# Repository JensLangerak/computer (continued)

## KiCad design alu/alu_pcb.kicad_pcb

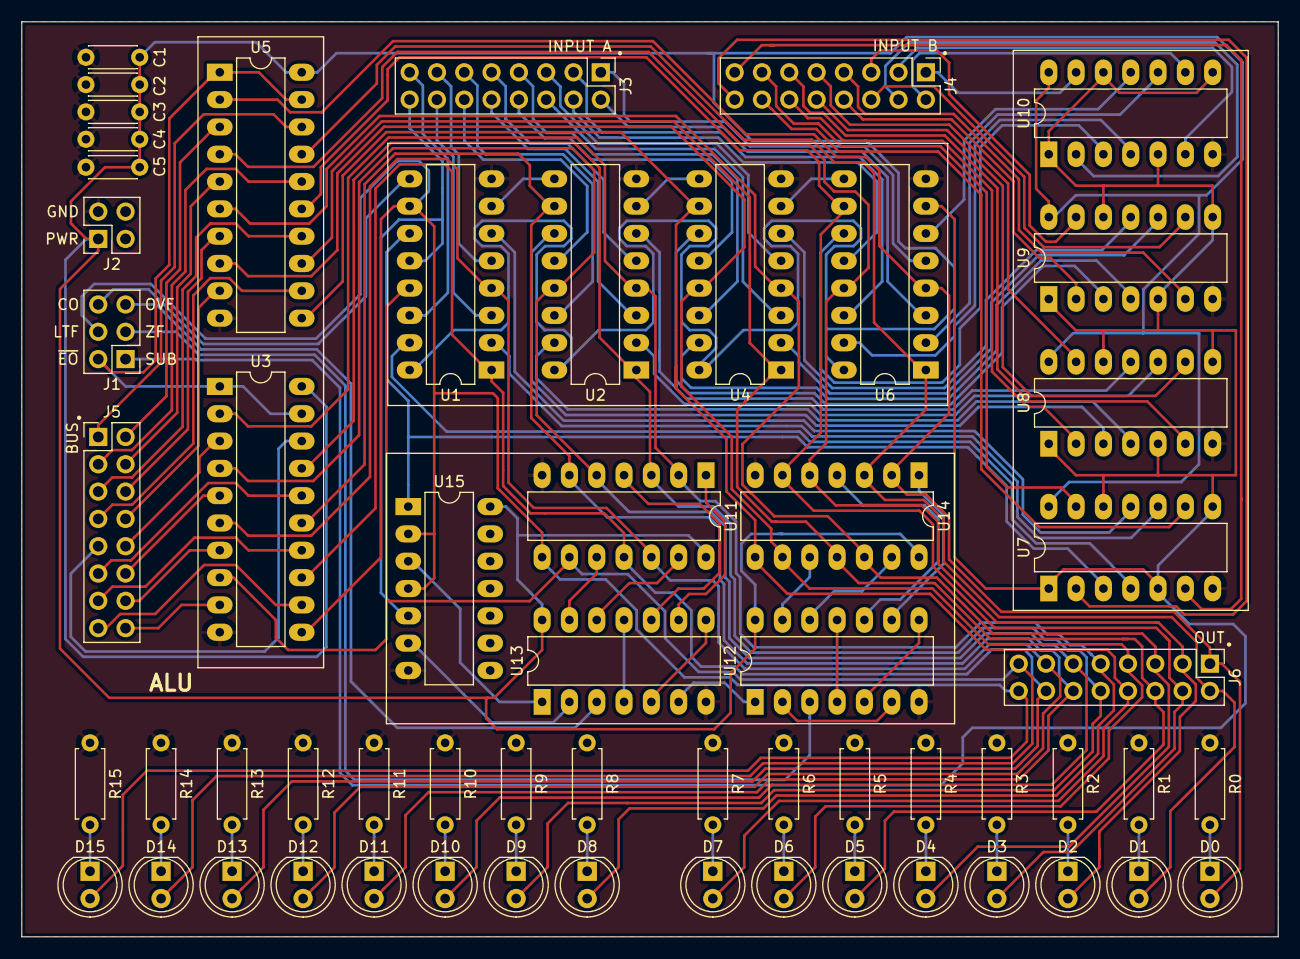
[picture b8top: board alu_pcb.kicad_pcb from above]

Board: 2 copper layers, 116.8 x 85.1 mm, 58 parts (0 on the bottom side), 122 nets.

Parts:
C1, C2, C3, C4, C5: 0.1µF; C_Disc_D4.3mm_W1.9mm_P5.00mm
D0, D1, D2, D3, D4, D5, D6, D7, D8, D9, D10, D11, D12, D13, D14, D15: LED_ALT; LED_D5.0mm
J1: Conn_02x03_Odd_Even; PinHeader_2x03_P2.54mm_Vertical
J2: Conn_02x02_Odd_Even; PinHeader_2x02_P2.54mm_Vertical
J3, J4, J5, J6: Conn_02x08_Odd_Even; PinHeader_2x08_P2.54mm_Vertical
R0, R1, R2, R3, R4, R5, R6, R7, R8, R9, R10, R11, R12, R13, R14, R15: 5k; R_Axial_DIN0207_L6.3mm_D2.5mm_P7.62mm_Horizontal
U1, U2, U4, U6: 74LS283; DIP-16_W7.62mm_LongPads
U3, U5: 74LS244; DIP-20_W7.62mm_LongPads
U7, U8, U9, U10: 74LS386; DIP-14_W7.62mm_LongPads
U11, U14: 74LS02; DIP-14_W7.62mm_LongPads
U12, U13: 74LS08; DIP-14_W7.62mm_LongPads
U15: 74LS00; DIP-14_W7.62mm_LongPads

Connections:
/ALU/CARRY_OUT: J1.6, U1.9
/ALU/D_BI0: U6.6, U10.11
/ALU/D_BI1: U6.2, U10.10
/ALU/D_BI2: U6.15, U10.4
/ALU/D_BI3: U6.11, U10.3
/ALU/D_BI4: U4.6, U9.11
/ALU/D_BI5: U4.2, U9.10
/ALU/D_BI6: U4.15, U9.4
/ALU/D_BI7: U4.11, U9.3
/ALU/D_BI8: U2.6, U8.11
/ALU/D_BI9: U2.2, U8.10
/ALU/D_BI10: U2.15, U8.4
/ALU/D_BI11: U2.11, U8.3
/ALU/D_BI12: U1.6, U7.11
/ALU/D_BI13: U1.2, U7.10
/ALU/D_BI14: U1.15, U7.4
/ALU/D_BI15: U1.11, U7.3, U15.1
/ALU/LTF: D15.2, J1.4, J6.16, U1.10, U3.11, U11.8, U15.2, U15.4
/ALU/OVF: J1.5, U13.3
/ALU/SUBTRACT: J1.1, U6.7, U7.1, U7.5, U7.8, U7.12, U8.1, U8.5, U8.8, U8.12, U9.1, U9.5, U9.8, U9.12, U10.1, U10.5, U10.8, U10.12
/ALU/ZF: J1.3, U12.3
/ALU/~ENALBE_OUTPUT~: J1.2, U3.1, U3.19, U5.1, U5.19
/CONN BUS A/D0: J3.1, U6.5
/CONN BUS A/D1: J3.2, U6.3
/CONN BUS A/D2: J3.3, U6.14
/CONN BUS A/D3: J3.4, U6.12
/CONN BUS A/D4: J3.5, U4.5
/CONN BUS A/D5: J3.6, U4.3
/CONN BUS A/D6: J3.7, U4.14
/CONN BUS A/D7: J3.8, U4.12
/CONN BUS A/D8: J3.9, U2.5
/CONN BUS A/D9: J3.10, U2.3
/CONN BUS A/D10: J3.11, U2.14
/CONN BUS A/D11: J3.12, U2.12
/CONN BUS A/D12: J3.13, U1.5
/CONN BUS A/D13: J3.14, U1.3
/CONN BUS A/D14: J3.15, U1.14
/CONN BUS A/D15: J3.16, U1.12, U15.5
/CONN BUS B/D0: J4.1, U10.13
/CONN BUS B/D1: J4.2, U10.9
/CONN BUS B/D2: J4.3, U10.6
/CONN BUS B/D3: J4.4, U10.2
/CONN BUS B/D4: J4.5, U9.13
/CONN BUS B/D5: J4.6, U9.9
/CONN BUS B/D6: J4.7, U9.6
/CONN BUS B/D7: J4.8, U9.2
/CONN BUS B/D8: J4.9, U8.13
/CONN BUS B/D9: J4.10, U8.9
/CONN BUS B/D10: J4.11, U8.6
/CONN BUS B/D11: J4.12, U8.2
/CONN BUS B/D12: J4.13, U7.13
/CONN BUS B/D13: J4.14, U7.9
/CONN BUS B/D14: J4.15, U7.6
/CONN BUS B/D15: J4.16, U7.2
/CONN BUS DATA/D0: J5.1, U5.18
/CONN BUS DATA/D1: J5.2, U5.3
/CONN BUS DATA/D2: J5.3, U5.16
/CONN BUS DATA/D3: J5.4, U5.5
/CONN BUS DATA/D4: J5.5, U5.14
/CONN BUS DATA/D5: J5.6, U5.7
/CONN BUS DATA/D6: J5.7, U5.12
/CONN BUS DATA/D7: J5.8, U5.9
/CONN BUS DATA/D8: J5.9, U3.18
/CONN BUS DATA/D9: J5.10, U3.3
/CONN BUS DATA/D10: J5.11, U3.16
/CONN BUS DATA/D11: J5.12, U3.5
/CONN BUS DATA/D12: J5.13, U3.14
/CONN BUS DATA/D13: J5.14, U3.7
/CONN BUS DATA/D14: J5.15, U3.12
/CONN BUS DATA/D15: J5.16, U3.9
/CONN BUS SUM/D0: D0.2, J6.1, U5.2, U6.4, U14.2
/CONN BUS SUM/D1: D1.2, J6.2, U5.17, U6.1, U14.3
/CONN BUS SUM/D2: D2.2, J6.3, U5.4, U6.13, U14.5
/CONN BUS SUM/D3: D3.2, J6.4, U5.15, U6.10, U14.6
/CONN BUS SUM/D4: D4.2, J6.5, U4.4, U5.6, U14.12
/CONN BUS SUM/D5: D5.2, J6.6, U4.1, U5.13, U14.11
/CONN BUS SUM/D6: D6.2, J6.7, U4.13, U5.8, U14.9
/CONN BUS SUM/D7: D7.2, J6.8, U4.10, U5.11, U14.8
/CONN BUS SUM/D8: D8.2, J6.9, U2.4, U3.2, U11.2
/CONN BUS SUM/D9: D9.2, J6.10, U2.1, U3.17, U11.3
/CONN BUS SUM/D10: D10.2, J6.11, U2.13, U3.4, U11.5
/CONN BUS SUM/D11: D11.2, J6.12, U2.10, U3.15, U11.6
/CONN BUS SUM/D12: D12.2, J6.13, U1.4, U3.6, U11.12
/CONN BUS SUM/D13: D13.2, J6.14, U1.1, U3.13, U11.11
/CONN BUS SUM/D14: D14.2, J6.15, U1.13, U3.8, U11.9
GND: C1.1, C2.1, C3.1, C4.1, C5.1, J2.2, R0.1, R1.1, R2.1, R3.1, R4.1, R5.1, R6.1, R7.1, R8.1, R9.1, R10.1, R11.1, R12.1, R13.1, R14.1, R15.1, U1.8, U2.8, U3.10, U4.8, U5.10, U6.8, U7.7, U8.7, U9.7, U10.7, U11.7, U12.7, U13.7, U14.7, U15.7
unnamed: D0.1, R0.2
unnamed: D1.1, R1.2
unnamed: D2.1, R2.2
unnamed: D3.1, R3.2
unnamed: D4.1, R4.2
unnamed: D5.1, R5.2
unnamed: D6.1, R6.2
unnamed: D7.1, R7.2
unnamed: D8.1, R8.2
unnamed: D9.1, R9.2
unnamed: D10.1, R10.2
unnamed: D11.1, R11.2
unnamed: D12.1, R12.2
unnamed: D13.1, R13.2
unnamed: D14.1, R14.2
unnamed: D15.1, R15.2
unnamed: U1.7, U2.9
unnamed: U2.7, U4.9
unnamed: U4.7, U6.9
unnamed: U11.1, U13.9
unnamed: U11.4, U13.10
unnamed: U11.10, U13.13
unnamed: U11.13, U13.12
unnamed: U12.1, U13.6
unnamed: U12.2, U12.6
unnamed: U12.5, U12.8
unnamed: U12.9, U14.1
unnamed: U12.10, U14.4
unnamed: U12.4, U12.11
unnamed: U12.12, U14.13
unnamed: U12.13, U14.10
unnamed: U13.1, U15.3
unnamed: U13.2, U15.6
unnamed: U13.5, U13.8
unnamed: U13.4, U13.11
VCC: C1.2, C2.2, C3.2, C4.2, C5.2, J2.1, U1.16, U2.16, U3.20, U4.16, U5.20, U6.16, U7.14, U8.14, U9.14, U10.14, U11.14, U12.14, U13.14, U14.14, U15.14

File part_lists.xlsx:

Reference | Quantity | Value | Footprint | Datasheet
C2 C3 C1 C4 | 4 | 0.1µF | Capacitor_THT:C_Disc_D4.3mm_W1.9mm_P5.00mm | ~
D15 D14 D13 D12 D11 D10 D9 D8 D7 D6 D5 D4 D3 D2 D0 D1 | 16 | LED_ALT | LED_THT:LED_D5.0mm | ~
J1 | 1 | Conn_02x03_Odd_Even | Connector_PinHeader_2.54mm:PinHeader_2x03_P2.54mm_Vertical | ~
J2 | 1 | Conn_02x02_Odd_Even | Connector_PinHeader_2.54mm:PinHeader_2x02_P2.54mm_Vertical | ~
J3 J4 J5 J6 | 4 | Conn_02x08_Odd_Even | Connector_PinHeader_2.54mm:PinHeader_2x08_P2.54mm_Vertical | ~
R2 R4 R5 R6 R7 R8 R9 R10 R11 R12 R13 R14 R15 R0 R1 R3 | 16 | 5k | Resistor_THT:R_Axial_DIN0207_L6.3mm_D2.5mm_P7.62mm_Horizontal | ~
U1 U2 U4 U6 | 4 | 74LS283 | Package_DIP:DIP-16_W7.62mm_LongPads | http://www.ti.com/lit/gpn/sn74LS283
U13 U12 | 2 | 74LS08 | Package_DIP:DIP-14_W7.62mm_LongPads | http://www.ti.com/lit/gpn/sn74LS08
U14 U11 | 2 | 74LS02 | Package_DIP:DIP-14_W7.62mm_LongPads | http://www.ti.com/lit/gpn/sn74ls02
U15 | 1 | 74LS00 | Package_DIP:DIP-14_W7.62mm_LongPads | http://www.ti.com/lit/gpn/sn74ls00
U3 U5 | 2 | 74LS244 | Package_DIP:DIP-20_W7.62mm_LongPads | http://www.ti.com/lit/gpn/sn74LS244
U8 U7 U10 U9 | 4 | 74LS386 | Package_DIP:DIP-14_W7.62mm_LongPads | http://www.ti.com/lit/gpn/sn74LS386

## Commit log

2020-05-14 add everything to git repo
2020-05-14 move alu to dir and create pcb project
2020-05-16 alu routed first iteration
2020-06-08 route alu, upde register
2020-06-14 ram pcb
2020-06-21 program counter
2020-07-14 way to long since last commit
2020-08-17 add bit operations
2020-08-25 memory programmer and cu
2020-08-26 connect cu and start creating material csv
2020-08-28 part lists
2021-10-12 Commit uncomitted changes. no clue what I had done last time
